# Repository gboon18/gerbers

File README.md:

# gerber files for PCB designs

## [Power Cable Tester](https://github.com/gboon18/gerbers/tree/main/PowerCableTester)
This is to test the cables manufactured by the vendor.
One end is the Fischer connector and the other end is the Power Breakout Board.

## [Power Fanout Board](https://github.com/gboon18/gerbers/tree/main/PowerFanoutBoard)
This is for the power distribution from multi-conductor cables to the Power Board and Readout Unit of the MVTX.

## [RB FanoutBoard](https://github.com/gboon18/gerbers/tree/main/RBFanoutBoard)
This distributes voltage drop sense of the reverse bias (RB), its interlock, and status.
All connections are RJ45.

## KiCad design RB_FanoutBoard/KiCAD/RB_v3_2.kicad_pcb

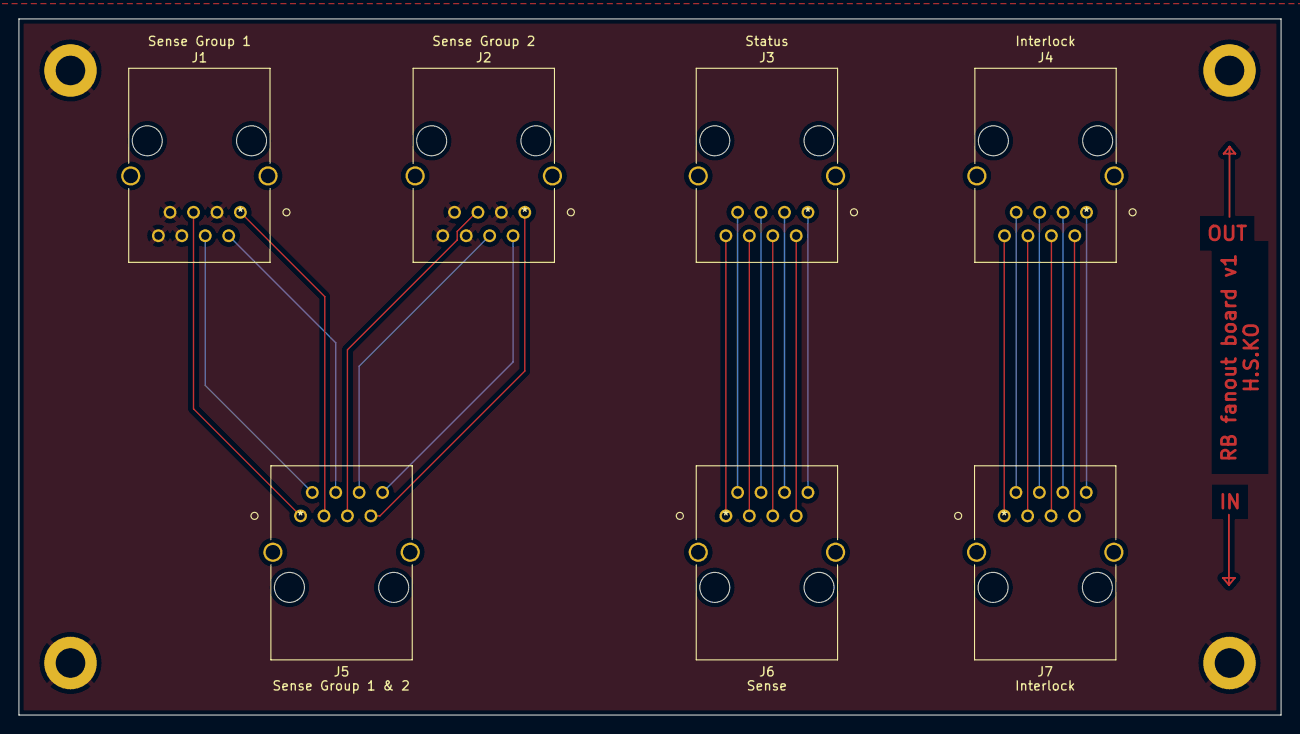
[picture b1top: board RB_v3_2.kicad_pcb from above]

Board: 2 copper layers, 136.8 x 75.4 mm, 7 parts (0 on the bottom side), 25 nets.

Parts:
J1: Sense Group 1; 44661-0021
J2: Sense Group 2; 44661-0021
J3: Status; 44661-0021
J4, J7: Interlock; 44661-0021
J5: Sense Group 1 & 2; 44661-0021
J6: Sense; 44661-0021

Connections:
GND: J1.3, J1.6, J1.7, J1.8, J2.3, J2.6, J2.7, J2.8
unnamed: J1.1, J5.3
unnamed: J1.2, J5.4
unnamed: J1.4, J5.2
unnamed: J1.5, J5.1
unnamed: J2.1, J5.7
unnamed: J2.2, J5.8
unnamed: J2.4, J5.6
unnamed: J2.5, J5.5
unnamed: J3.1, J6.8
unnamed: J3.2, J6.7
unnamed: J3.3, J6.6
unnamed: J3.4, J6.5
unnamed: J3.5, J6.4
unnamed: J3.6, J6.3
unnamed: J3.7, J6.2
unnamed: J3.8, J6.1
unnamed: J4.1, J7.8
unnamed: J4.2, J7.7
unnamed: J4.3, J7.6
unnamed: J4.4, J7.5
unnamed: J4.5, J7.4
unnamed: J4.6, J7.3
unnamed: J4.7, J7.2
unnamed: J4.8, J7.1

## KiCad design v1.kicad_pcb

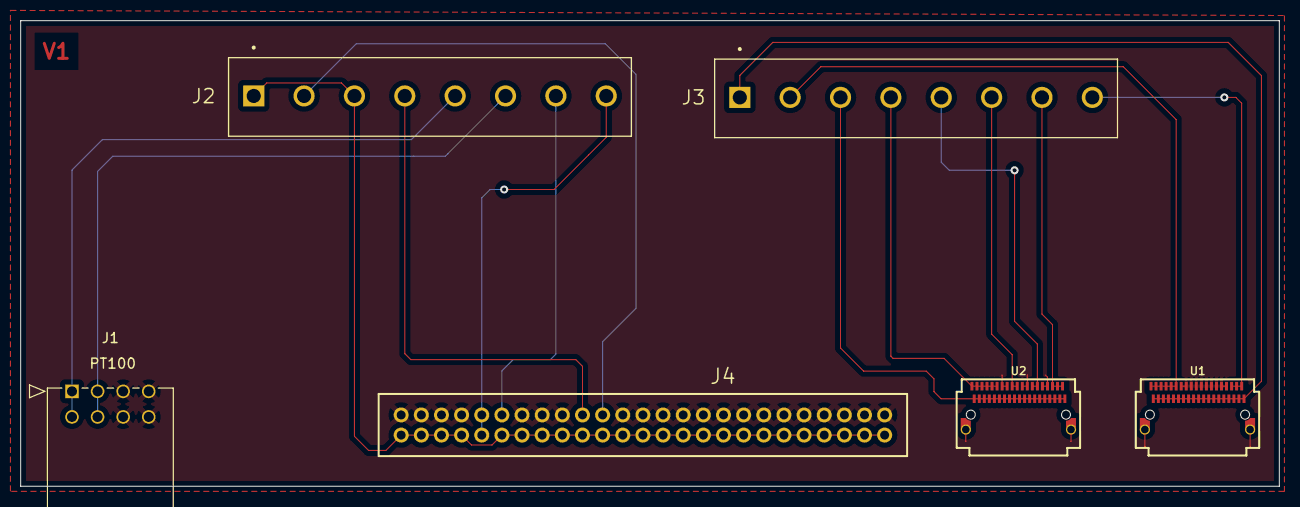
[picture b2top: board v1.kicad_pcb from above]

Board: 2 copper layers, 125.0 x 46.2 mm, 6 parts (0 on the bottom side), 16 nets.

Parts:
J1: PT100; 901303108
J2: Side_BreakoutBoard; CUI_TB003-500-P08BE
J3: Side_SAMTEC; CUI_TB003-500-P08BE
J4: BreakoutBoard_main; SAMTEC-LS2-125-01-X-D
U1: SAMTEC_Digi; UEC5-019-1-X-D-RA-1-A
U2: SAMTEC_Anal; UEC5-019-1-X-D-RA-1-A

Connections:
GND: J1.5, J1.6, J1.7, J1.8, J4.2, J4.4, J4.6, J4.8, J4.10, J4.12, J4.14, J4.16, J4.18, J4.20, J4.22, J4.24, J4.26, J4.28, J4.34, J4.36, J4.38, J4.44, J4.46, J4.48, J4.50, U1.A7, U1.A8, U1.A9, U1.A10, U1.A11, U1.A12, U1.A13, U1.A14, U1.A15, U1.A16, U1.G1, U1.G2, U2.A7, U2.A8, U2.A11, U2.A12, U2.A15, U2.A16, U2.G1, U2.G2
unnamed: J1.1, J1.2, J2.5
unnamed: J1.3, J1.4, J2.6
unnamed: J2.1, J2.3, J4.1, J4.3, J4.5, J4.7, J4.9, J4.11, J4.13, J4.15, J4.17, J4.19, J4.21, J4.23, J4.25, J4.27, J4.29, J4.31, J4.33, J4.35, J4.37, J4.39, J4.43, J4.45, J4.47, J4.49
unnamed: J2.2, J4.30
unnamed: J2.4, J4.32
unnamed: J2.7, J4.40
unnamed: J2.8, J4.41, J4.42
unnamed: J3.1, U1.B1, U1.B2, U1.B3, U1.B4, U1.B5, U1.B6, U1.B7, U1.B8, U1.B9, U1.B10, U1.B11, U1.B12, U1.B13, U1.B14, U1.B15, U1.B16, U1.B17, U1.B18, U1.B19
unnamed: J3.2, U1.A1, U1.A2, U1.A3, U1.A4, U1.A5, U1.A6
unnamed: J3.3, U2.B1, U2.B2, U2.B3, U2.B4, U2.B5, U2.B6, U2.B7, U2.B8, U2.B9, U2.B10, U2.B11, U2.B12, U2.B13, U2.B14, U2.B15, U2.B16, U2.B17, U2.B18, U2.B19
unnamed: J3.4, U2.A1, U2.A2, U2.A3, U2.A4, U2.A5, U2.A6
unnamed: J3.5, U2.A13, U2.A14
unnamed: J3.6, U2.A9, U2.A10
unnamed: J3.7, U2.A17, U2.A18, U2.A19
unnamed: J3.8, U1.A17, U1.A18, U1.A19

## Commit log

2023-05-10 Gerber image
2023-05-10 Update README.md with images
2023-05-10 Update README.md with image

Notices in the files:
parts and their libraries:
Copyright 2021 Accelerated Designs. All rights reserved.
